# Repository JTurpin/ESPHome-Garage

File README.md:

# ESPHome Based Garage Monitor

## Introduction
I built this circuit board to monitor my garage as well as control the garage door opener. This board is capable of reading door state through a switch, controlling the door, and using a BME680 to measure, temperature, humidity, volatile organic compounds (combustible gasses), and carbon dioxide.

## Hardware
Custom PCB created in Eagle CAD. I had these run at [seeedstudio-fusion](https://www.seeedstudio.com/fusion_pcb.html). The boards have been tested and are currently functioning in my garage.

## Interfacing with the garage door opener
There are inputs and outputs to read and control up to two doors. The ```DoorX-In``` are a simple digital read. I use magnetic reed switches that are normally open for this. They can be had cheaply as many alarm system used the for door and window sensors like [this](https://www.amazon.com/VictorsHome-Magnetic-Surface-Adhesive-Security/dp/B094XJ7K8K).

To controll the door simply run a 2 conductor wire from the ```DoorX`` screw terminals to the same terminals that the wall switch mounted inside the garage is connected to.

## Home Assistant Configuration
ESPHome needs to be installed and functioning:
1) Click on ```+ NEW DEVICE```
1) Click ```Continue```
2) Give it a name, I chose ```garage-monitor```
3) Select ```Pick specific board``` and ```Wemos D1 and Wemos D1 mini```
4) Select ```Skip```
5) Find the device and click ```EDIT```
6) Paste in the [yaml](ESPHome/garage-sensor.yaml) file and edit the proper wifi setting.

## Automations
I use NodeRed to automate many aspects of my smart home. Here are a couple related to my garage to get you going.
- Notify via pushover if the garage door is open for 15 minutes [json](NodeRed%20Flows/notify-door-open.json) 
- Quick reset the output on the "button push" (There is probably a better way to do this but I found this to be effective) [json](NodeRed%20Flows/quick-trigger.json) 

## To Do...
There's two WS2812b on the board that I haven't found a use for yet, they could be used for a number of things though. examples:
- Countdown timer until autmoated shut of garage door
- Gauge estimates like [this](images/lovelace_gauge_segments.png) for Temp, VOC, Humidity, CO2.
- etc

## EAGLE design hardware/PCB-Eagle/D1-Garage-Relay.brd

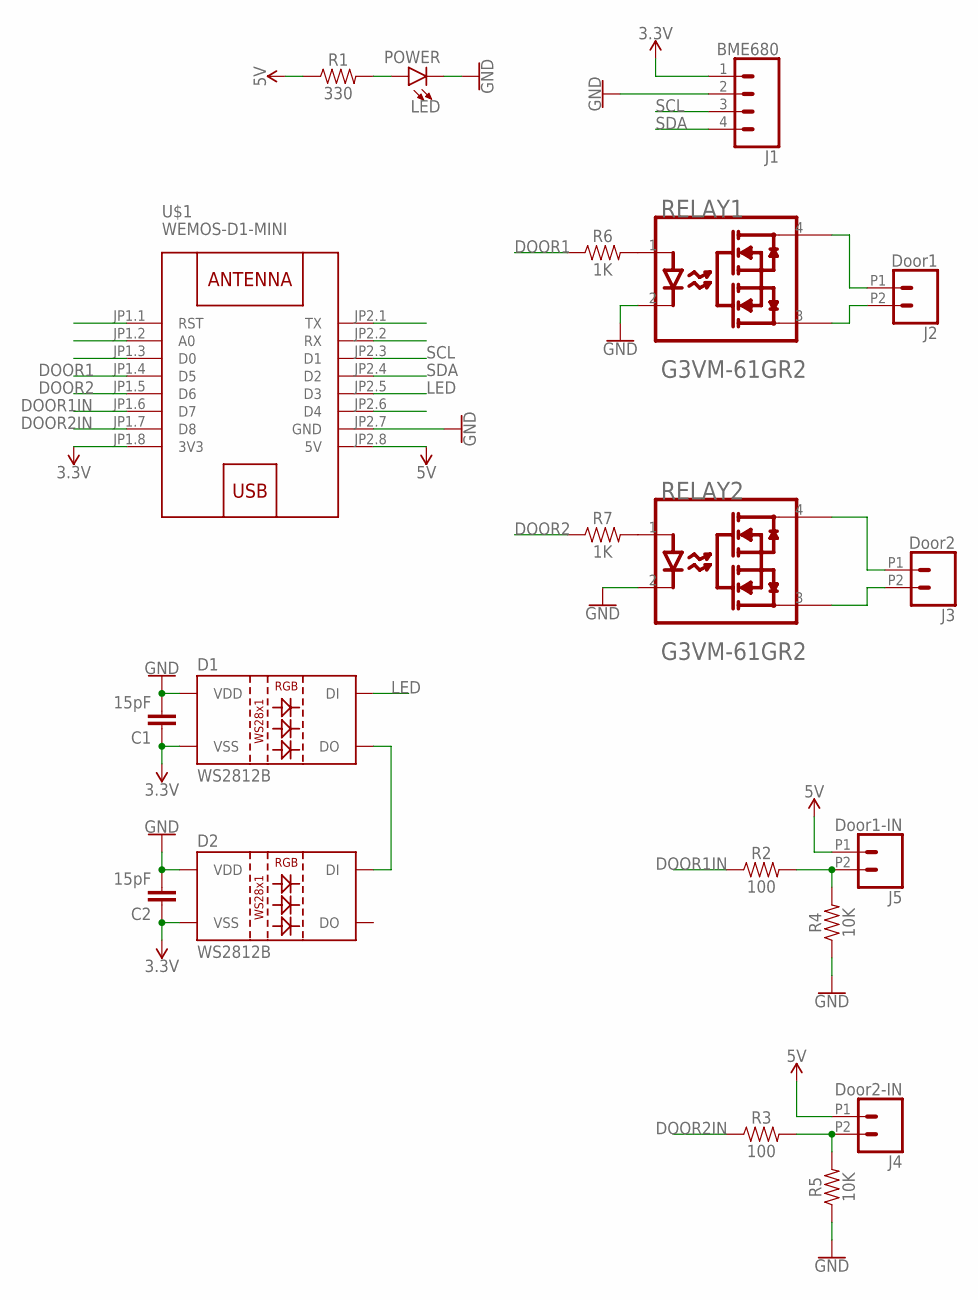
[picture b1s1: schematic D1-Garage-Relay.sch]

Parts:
C1, C2: 15pF; 0603
D1, D2: WS2812B
J1: BME680; 1X04
J2: Door1; 1X02_2.54_SCREWTERM
J3: Door2; 1X02_2.54_SCREWTERM
J4: Door2-IN; 1X02_2.54_SCREWTERM
J5: Door1-IN; 1X02_2.54_SCREWTERM
LED: POWER; LED-1206
R1: 330; 0603
R2, R3: 100; 0603
R4, R5: 10K; 0603
R6, R7: 1K; 0603
RELAY1, RELAY2: AQY282SZ; OMRON_G3VM-61GR2_3
U$1: WEMOS-D1-MINI

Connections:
3.3V: C1.1, C2.1, D1.3 (VSS), D2.3 (VSS), J1.1, U$1.JP1.8 (3V3)
5V: J4.P1 (1), J5.P1 (1), R1.1, U$1.JP2.8 (5V)
DOOR1: R6.1, U$1.JP1.4 (D5)
DOOR1IN: R2.1, U$1.JP1.6 (D7)
DOOR2: R7.1, U$1.JP1.5 (D6)
DOOR2IN: R3.1, U$1.JP1.7 (D8)
GND: C1.2, C2.2, D1.1 (VDD), D2.1 (VDD), J1.2, LED.C, R4.1, R5.1, RELAY1.2 (CATHODE), RELAY2.2 (CATHODE), U$1.JP2.7 (GND)
LED: D1.4 (DI), U$1.JP2.5 (D3)
unnamed: J2.P2 (2), RELAY1.3 (1_DRAIN)
unnamed: J3.P2 (2), RELAY2.3 (1_DRAIN)
unnamed: J2.P1 (1), RELAY1.4 (2_DRAIN)
unnamed: R6.2, RELAY1.1 (ANODE)
unnamed: J3.P1 (1), RELAY2.4 (2_DRAIN)
unnamed: R7.2, RELAY2.1 (ANODE)
unnamed: LED.A, R1.2
unnamed: J5.P2 (2), R2.2, R4.2
unnamed: J4.P2 (2), R3.2, R5.2
unnamed: D1.2 (DO), D2.4 (DI)
SCL: J1.3, U$1.JP2.3 (D1)
SDA: J1.4, U$1.JP2.4 (D2)

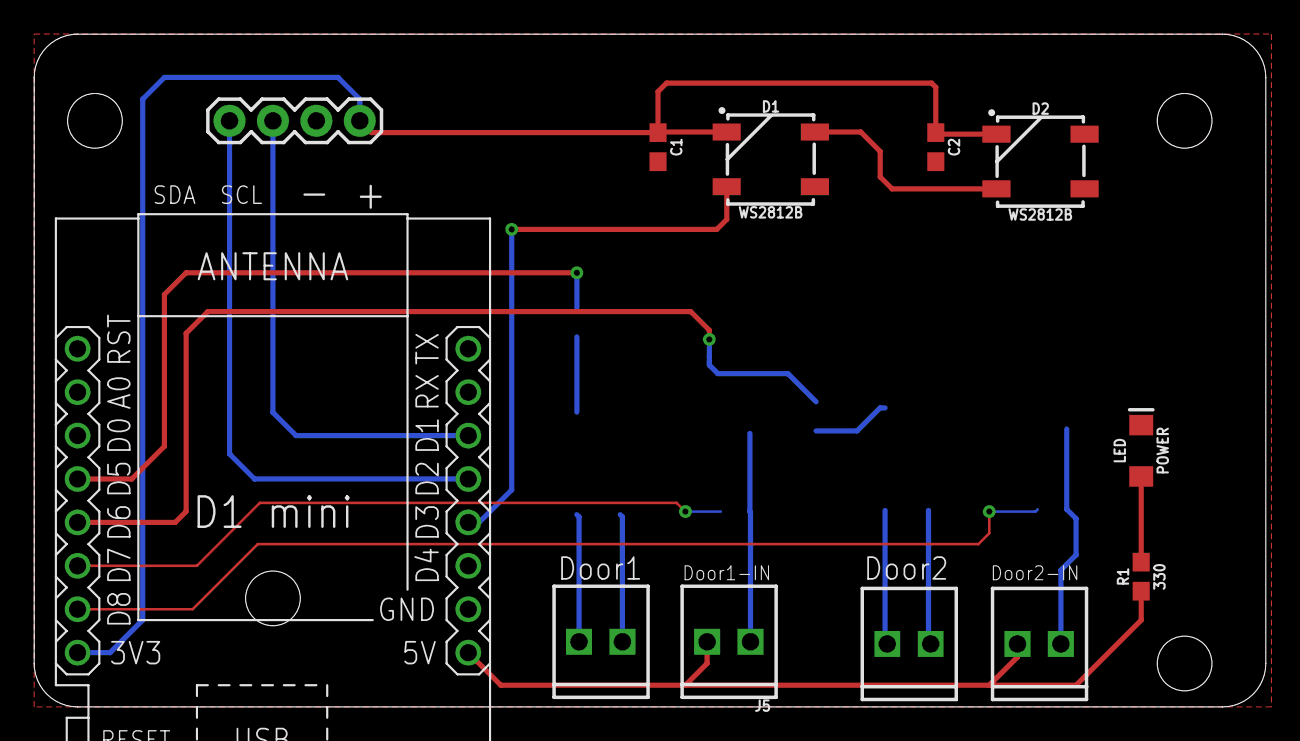
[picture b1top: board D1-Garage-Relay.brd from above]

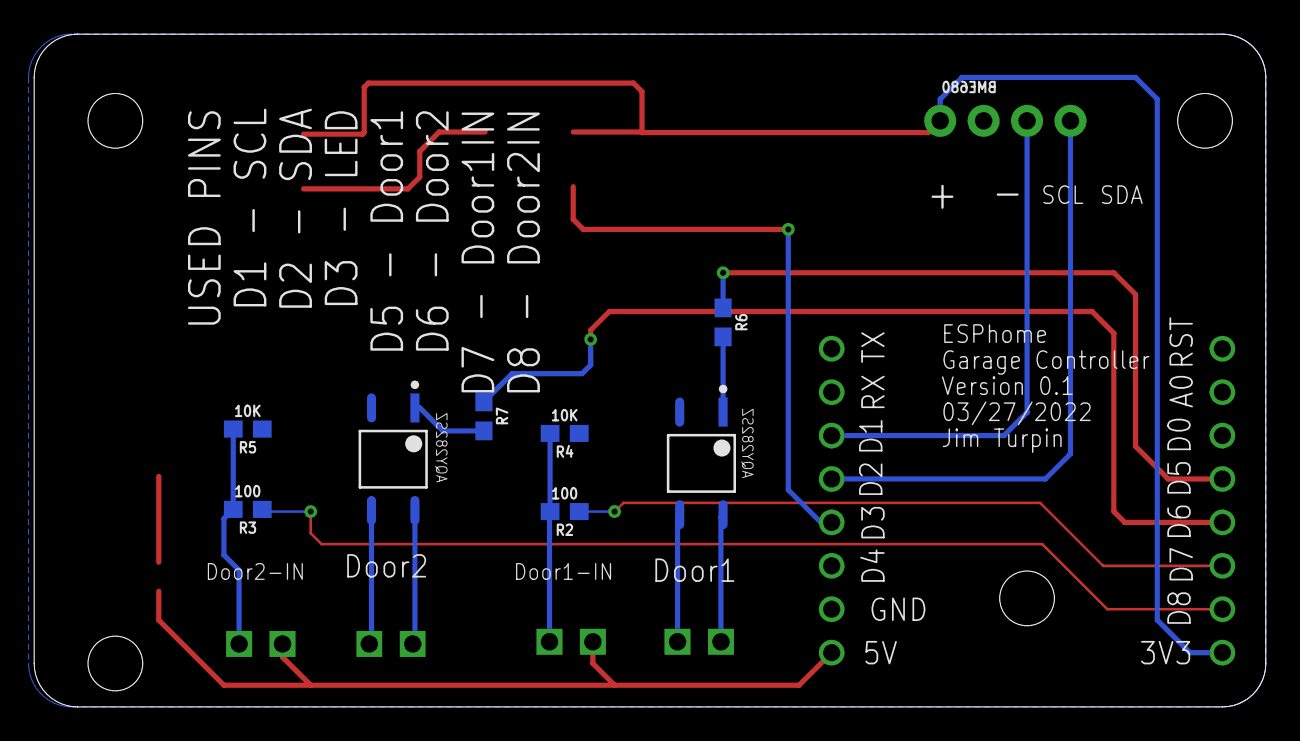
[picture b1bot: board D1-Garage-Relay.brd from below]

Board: 2 copper layers, 72.1 x 39.4 mm, 20 parts (8 on the bottom side), 20 nets.

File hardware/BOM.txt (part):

Partlist exported from Eagle

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
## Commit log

2022-05-21 adding in automations via node red
2022-05-21 adding images of the PCB
2022-05-22 adjusted bottom layer to accomodate documentation
2022-05-22 fixing a small typo

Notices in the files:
parts and their libraries:
diy-modules: Released under the Creative Commons Attribution 4.0 International License: http://creativecommons.org/licenses/by/4.0
SparkFun-Connectors: Licensing: Creative Commons ShareAlike 4.0 International - https://creativecommons.org/licenses/by-sa/4.0
